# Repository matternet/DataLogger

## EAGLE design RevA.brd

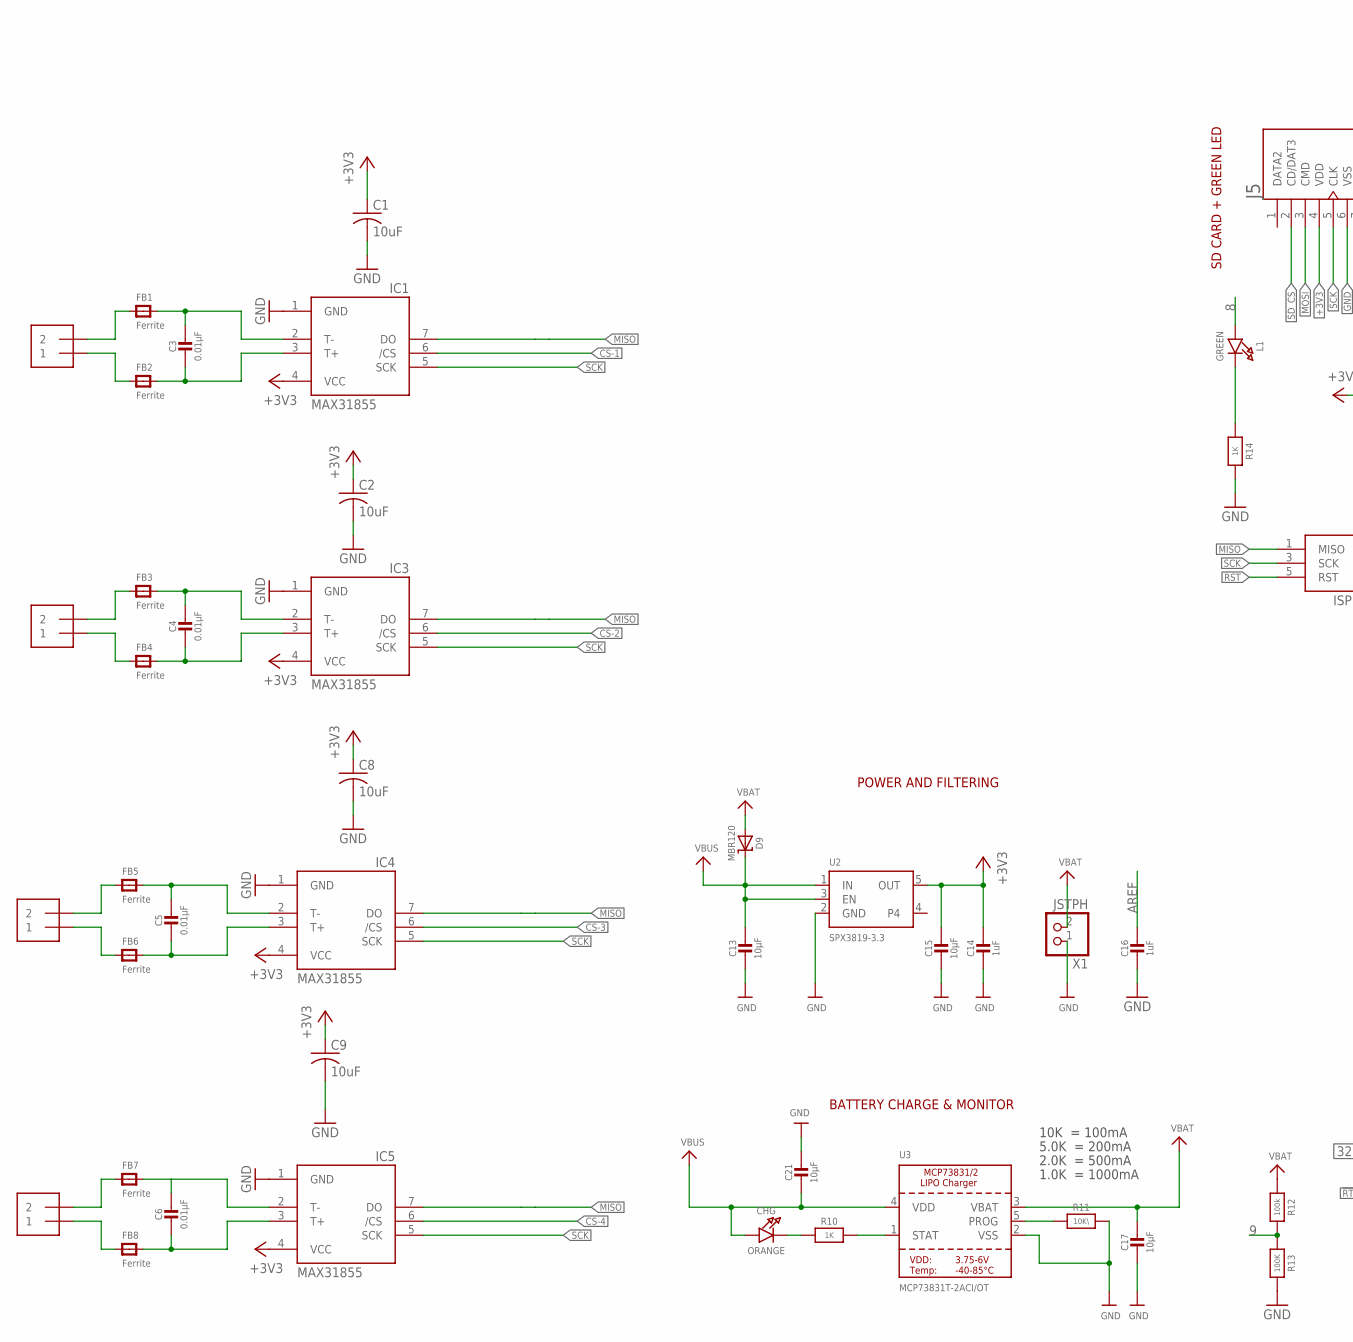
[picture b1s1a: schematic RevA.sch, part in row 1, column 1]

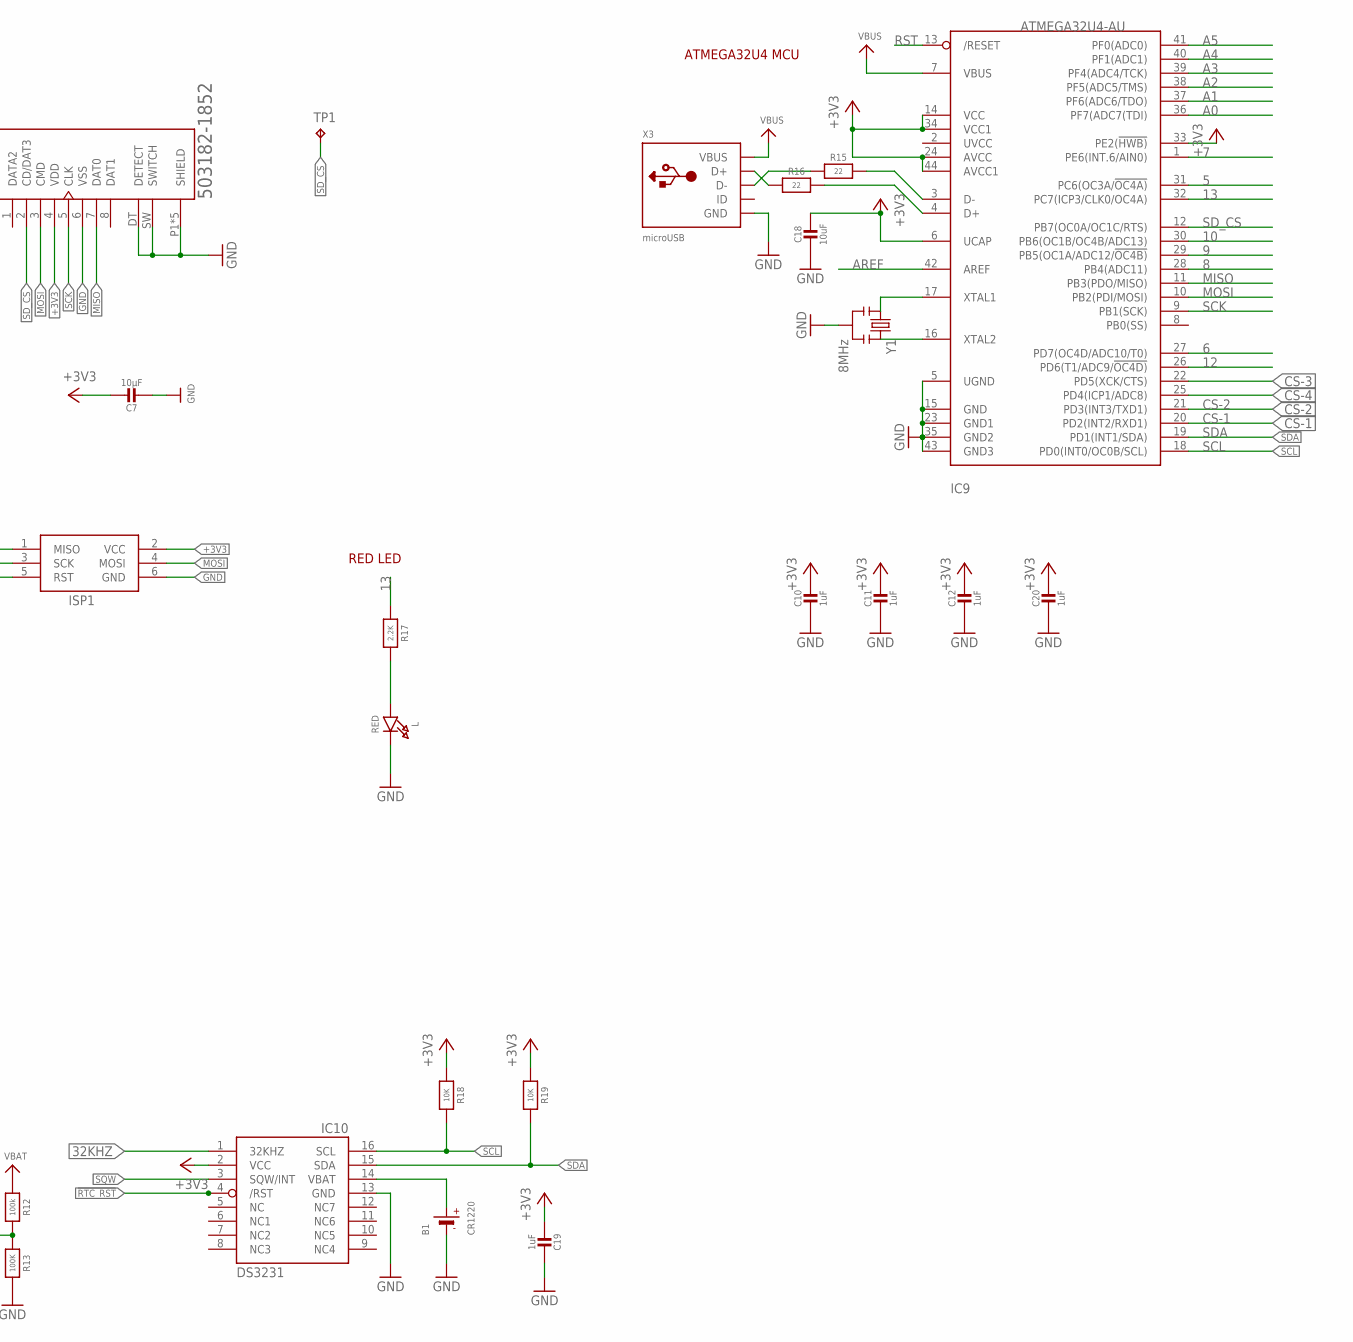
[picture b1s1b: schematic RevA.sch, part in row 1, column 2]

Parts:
B1: CR1220
C1, C2, C8, C9: 10uF; C0805K
C3, C4, C5, C6: 0.01µF; _0805
C7, C13, C15, C17, C21: 10µF; 0805-NO
C10, C11, C12, C14, C16, C20: 1uF; 0603-NO
C18: 10uF; 0805-NO
C19: 1uF; 0805-NO
CHG: ORANGE; CHIPLED_0805_NOOUTLINE
D9: MBR120; SOD-123
FB1, FB2, FB3, FB4, FB5, FB6, FB7, FB8: Ferrite; _0805
IC1, IC3, IC4, IC5: MAX31855; SO08
IC9: ATMEGA32U4-AU; TQFP44
IC10: DS3231/SO; SO16W
ISP1: AVRISP-BOX
J1, J2, J3, J4: 1X2-3.5MM
J5: 503182-1852; MOLEX_503182-1852
L: RED; CHIPLED_0805_NOOUTLINE
L1: GREEN; CHIPLED_0805_NOOUTLINE
R10, R14: 1K; 0603-NO
R11: 10K\; 0603-NO
R12: 100k; _0603MP
R13: 100K; _0603MP
R15, R16: 22; 0603-NO
R17: 2.2K; 0603-NO
R18, R19: 10K; 0805-NO
TP1: TPPAD1-13; P1-13
U2: SPX3819-3.3; SOT23-5
U3: MCP73831T-2ACI/OT; SOT23-5
X1: JSTPH; JSTPH2
X3: microUSB; 4UCONN_20329_V2
Y1: 8MHz; RESONATOR-SMD

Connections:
5: IC9.31 (PC6(OC3A/!OC4A))
6: IC9.27 (PD7(OC4D/ADC10/T0))
7: IC9.1 (PE6(INT.6/AIN0))
8: IC9.28 (PB4(ADC11)), L1.A
9: IC9.29 (PB5(OC1A/ADC12/!OC4B)), R12.2, R13.1
10: IC9.30 (PB6(OC1B/OC4B/ADC13))
12: IC9.26 (PD6(T1/ADC9/!OC4D))
13: IC9.32 (PC7(ICP3/CLK0/OC4A)), R17.1
32KHZ: IC10.1 (32KHZ)
!RTC_RST: IC10.4 (/RST)
+3V3: C1.1, C2.1, C7.1, C8.1, C9.1, C10.1, C11.1, C12.1, C14.1, C15.1, C18.1, C19.2, C20.1, IC1.4 (VCC), IC3.4 (VCC), IC4.4 (VCC), IC5.4 (VCC), IC9.6 (UCAP), IC9.14 (VCC), IC9.24 (AVCC), IC9.33 (PE2(!HWB)), IC9.34 (VCC1), IC9.44 (AVCC1), IC10.2 (VCC), ISP1.2 (VCC), J5.4 (VDD), R18.1, R19.1, U2.5 (OUT)
A0: IC9.36 (PF7(ADC7(TDI))
A1: IC9.37 (PF6(ADC6/TDO))
A2: IC9.38 (PF5(ADC5/TMS))
A3: IC9.39 (PF4(ADC4/TCK))
A4: IC9.40 (PF1(ADC1))
A5: IC9.41 (PF0(ADC0))
AREF: C16.1, IC9.42 (AREF)
CS-1: IC1.6 (/CS), IC9.20 (PD2(INT2/RXD1))
CS-2: IC3.6 (/CS), IC9.21 (PD3(INT3/TXD1))
CS-3: IC4.6 (/CS), IC9.22 (PD5(XCK/CTS))
CS-4: IC5.6 (/CS), IC9.25 (PD4(ICP1/ADC8))
D+: IC9.4 (D+), R16.2
D-: IC9.3 (D-), R15.2
GND: B1.-, C1.2, C2.2, C7.2, C8.2, C9.2, C10.2, C11.2, C12.2, C13.2, C14.2, C15.2, C16.2, C17.2, C18.2, C19.1, C20.2, C21.1, IC1.1 (GND), IC3.1 (GND), IC4.1 (GND), IC5.1 (GND), IC9.5 (UGND), IC9.15 (GND), IC9.23 (GND1), IC9.35 (GND2), IC9.43 (GND3), IC10.13 (GND), ISP1.6 (GND), J5.6 (VSS), J5.DT (DETECT), J5.P1 (SHIELD), J5.P2 (SHIELD), J5.P3 (SHIELD), J5.P4 (SHIELD), J5.P5 (SHIELD), J5.SW (SWITCH), L.C, R11.2, R13.2, R14.2, U2.2 (GND), U3.2 (VSS), X1.1, X3.BASE@1 (GND), X3.BASE@2 (GND), X3.GND, X3.SPRT@1 (GND), X3.SPRT@2 (GND), X3.SPRT@3 (GND), X3.SPRT@4 (GND), Y1.2
MISO: IC1.7 (DO), IC3.7 (DO), IC4.7 (DO), IC5.7 (DO), IC9.11 (PB3(PDO/MISO)), ISP1.1 (MISO), J5.7 (DAT0)
MOSI: IC9.10 (PB2(PDI/MOSI)), ISP1.4 (MOSI), J5.3 (CMD)
unnamed: FB1.1, J1.2
unnamed: FB3.1, J2.2
unnamed: C4.1, FB3.2, IC3.2 (T-)
unnamed: C3.1, FB1.2, IC1.2 (T-)
unnamed: FB2.1, J1.1
unnamed: C3.2, FB2.2, IC1.3 (T+)
unnamed: FB4.1, J2.1
unnamed: C4.2, FB4.2, IC3.3 (T+)
unnamed: FB5.1, J3.2
unnamed: C5.1, FB5.2, IC4.2 (T-)
unnamed: FB6.1, J3.1
unnamed: C5.2, FB6.2, IC4.3 (T+)
unnamed: FB7.1, J4.2
unnamed: C6.1, FB7.2, IC5.2 (T-)
unnamed: FB8.1, J4.1
unnamed: C6.2, FB8.2, IC5.3 (T+)
unnamed: CHG.C, R10.1
unnamed: R10.2, U3.1 (STAT)
unnamed: R11.1, U3.5 (PROG)
unnamed: L1.C, R14.1
unnamed: IC9.16 (XTAL2), Y1.3
unnamed: IC9.17 (XTAL1), Y1.1
unnamed: R16.1, X3.D+
unnamed: R15.1, X3.D-
unnamed: L.A, R17.2
RST: IC9.13 (/RESET), ISP1.5 (RST)
SCK: IC1.5 (SCK), IC3.5 (SCK), IC4.5 (SCK), IC5.5 (SCK), IC9.9 (PB1(SCK)), ISP1.3 (SCK), J5.5 (CLK)
SCL: IC9.18 (PD0(INT0/OC0B/SCL)), IC10.16 (SCL), R18.2
SDA: IC9.19 (PD1(INT1/SDA)), IC10.15 (SDA), R19.2
SD_CS: IC9.12 (PB7(OC0A/OC1C/RTS)), J5.2 (CD/DAT3), TP1.TP
SQW: IC10.3 (SQW/INT)
VBAT: C17.1, D9.A, R12.1, U3.3 (VBAT), X1.2
VBUS: C13.1, C21.2, CHG.A, D9.C, IC9.7 (VBUS), U2.1 (IN), U2.3 (EN), U3.4 (VDD), X3.VBUS
VCR: B1.+$1 (+), IC10.14 (VBAT)

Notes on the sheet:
POWER AND FILTERING
10K = 100mA
5.0K = 200mA
2.0K = 500mA
1.0K = 1000mA
BATTERY CHARGE & MONITOR
SD CARD + GREEN LED
ATMEGA32U4 MCU
RED LED

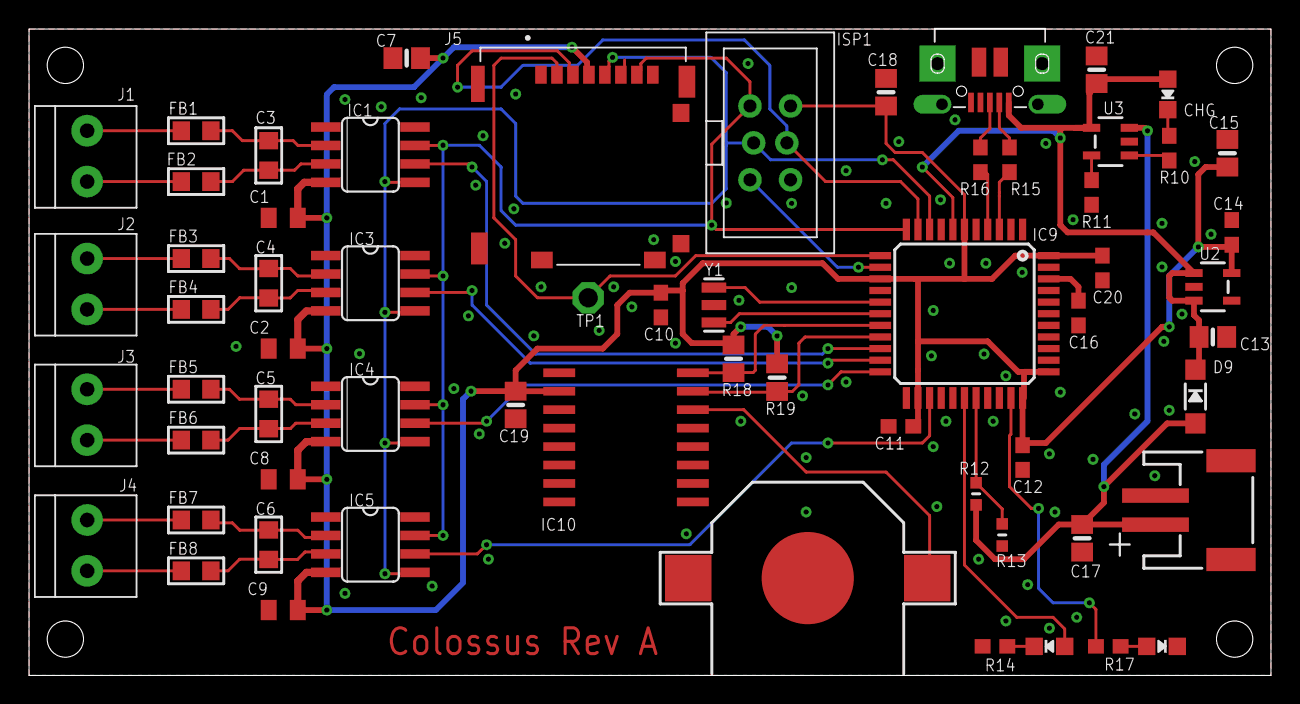
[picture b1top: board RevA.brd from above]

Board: 2 copper layers, 85.5 x 44.5 mm, 62 parts (0 on the bottom side), 47 nets.

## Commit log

2018-08-14 Initializing all data
2018-08-14 Last save
2018-08-14 Changes after review
2018-08-15 Added new layout scheme
2018-08-15 End of day
2018-08-15 Finalized layout and added libraries
2018-08-15 Increased power track widths
2018-08-16 Minor cosmetic changes
2018-08-16 More Revision
2018-08-16 Changed Layout
2018-08-17 Removed crossovers in traces
2018-08-17 Reduced Footprint
2018-08-18 Added BOM
2018-08-18 Final Traces
2018-08-18 Cleaned up the layout
2018-08-20 Final cleanup
2018-08-22 Adding gerber files
2018-08-22 removing redundant files
2018-09-19 Added Code Base
2018-09-21 Modifying RT code
2018-09-21 Modified the RTC code
2018-12-28 Added more functionality to the board

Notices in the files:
parts and their libraries:
SparkFun: Licensing: CC v3.0 Share-Alike You are welcome to use this library for commercial purposes.
